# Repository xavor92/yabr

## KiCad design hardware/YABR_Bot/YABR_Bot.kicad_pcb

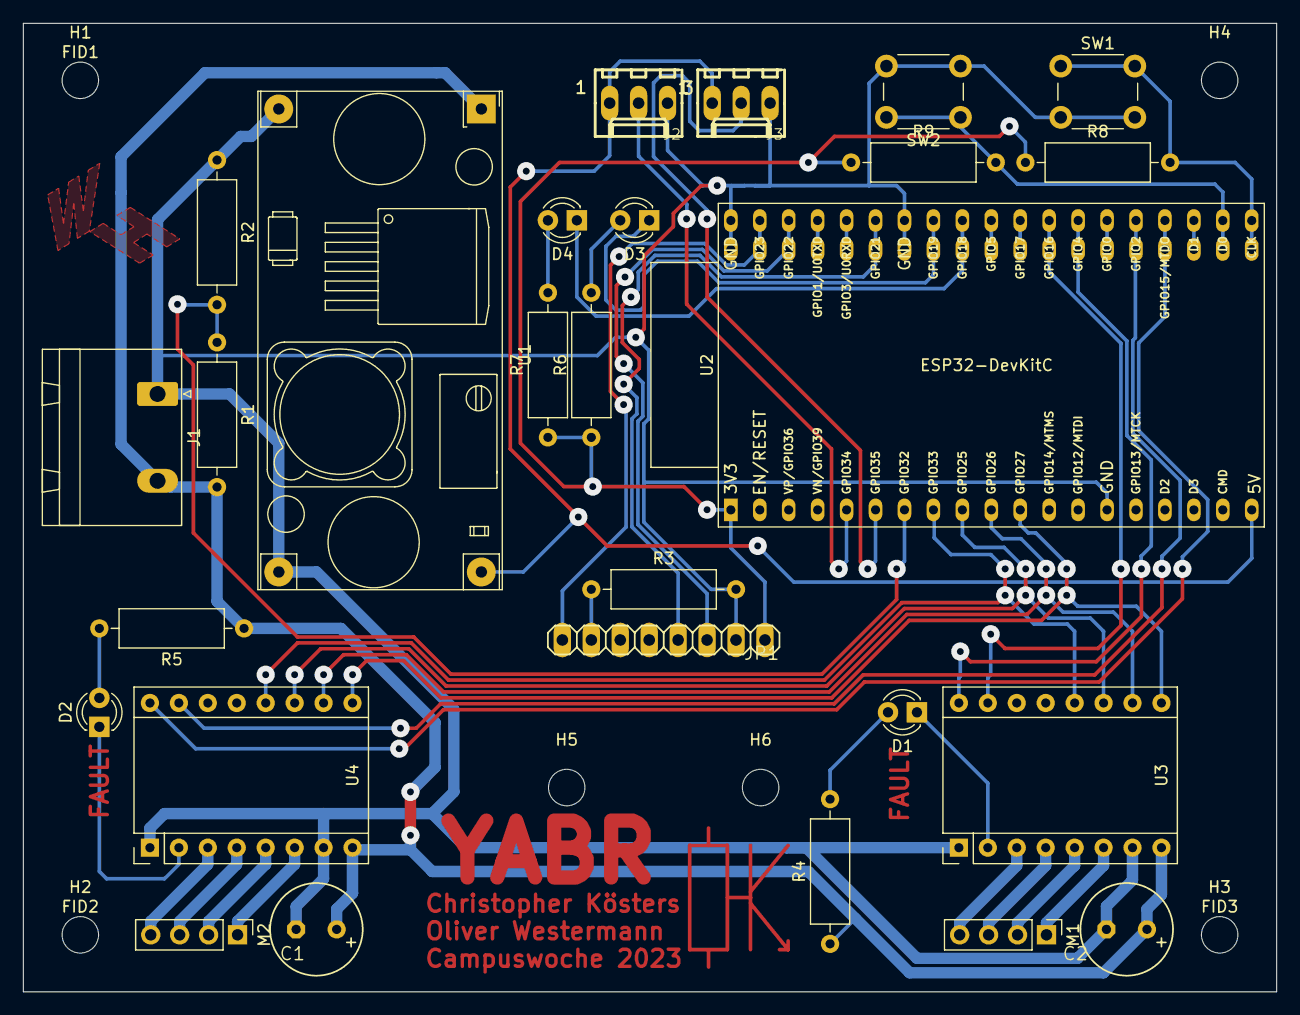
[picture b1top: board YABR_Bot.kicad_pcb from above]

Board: 2 copper layers, 110.0 x 85.0 mm, 36 parts (0 on the bottom side), 37 nets.

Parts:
C1, C2: 100uF/25V; E3,5-8
D1, D2, D3, D4: LED; LED_D3.0mm
FID1, FID2, FID3: Fiducial; Fiducial_1.5mm_Mask3mm
H1, H2, H3, H4, H5, H6: MountingHole; MountingHole_3.2mm_M3
J1: Conn_01x02_Socket; PhoenixContact_GMSTBA_2,5_2-G-7,62_1x02_P7.62mm_Horizontal
J2, J3: SERVO; 6410-03
JP1: ITG-MPU; 1X08
M1, M2: Stepper_Motor_bipolar; PinHeader_1x04_P2.54mm_Vertical
R1: 4k7; R_Axial_DIN0309_L9.0mm_D3.2mm_P12.70mm_Horizontal
R2: 3k3; R_Axial_DIN0309_L9.0mm_D3.2mm_P12.70mm_Horizontal
R3: 4K7; R_Axial_DIN0309_L9.0mm_D3.2mm_P12.70mm_Horizontal
R4, R5, R8, R9: 1K1; R_Axial_DIN0309_L9.0mm_D3.2mm_P12.70mm_Horizontal
R6, R7: 82; R_Axial_DIN0309_L9.0mm_D3.2mm_P12.70mm_Horizontal
SW1, SW2: SW_Push; SW_PUSH_6mm_H9.5mm
U1: DCDC_StepDown_LM2596
U2: ESP32-DevKitC
U3, U4: DRV8825; DRV8825_Breakout_15.2x20.3mm

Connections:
+3V3: JP1.1, R6.1, R7.1, R8.1, R9.1, U2.1 (3V3)
+5V: J2.1 (S), J3.1 (S), U1.4 (Vout), U2.19 (5V)
/AD0: JP1.7, R3.1
/DIR1: U2.26 (ADC2_CH0/GPIO4), U3.16 (DIR)
/DIR2: U2.23 (MTDO/GPIO15/ADC2_CH3), U4.16 (DIR)
/SCL: JP1.3, U2.36 (GPIO22)
/SDA: JP1.4, U2.33 (GPIO21)
/SERVO1: J2.2 (S), U2.5 (VDET_1/GPIO34/ADC1_CH6)
/SERVO2: J3.2 (S), U2.6 (VDET_2/GPIO35/ADC1_CH7)
/STEP_ENABLE: U2.11 (ADC2_CH7/GPIO27), U3.9 (EN), U4.9 (EN)
/STEP_SELECT_M0: U2.10 (DAC_2/ADC2_CH9/GPIO26), U3.10 (M0), U4.10 (M0)
/STEP_SELECT_M1: U2.9 (DAC_1/ADC2_CH8/GPIO25), U3.11 (M1), U4.11 (M1)
/STEP_SELECT_M2: U2.8 (32K_XN/GPIO33/ADC1_CH5), U3.12 (M2), U4.12 (M2)
/STP1: U2.27 (GPIO16), U3.15 (STP)
/STP2: U2.24 (ADC2_CH2/GPIO2), U4.15 (STP)
/VSENS: R1.1, R2.2, U2.7 (32K_XP/GPIO32/ADC1_CH4)
GND: C1.-, C2.-, J1.1, J2.3 (S), J3.3 (S), JP1.2, R2.1, R3.2, SW1.2, SW2.2, U1.2 (GND), U1.3 (GND), U2.14 (GND), U2.32 (GND), U2.38 (GND), U3.1 (GND), U3.7 (GND), U4.1 (GND), U4.7 (GND)
unnamed: D1.2 (A), R4.2
unnamed: D1.1 (K), U3.2 (FLT)
unnamed: D2.2 (A), R5.2
unnamed: D2.1 (K), U4.2 (FLT)
unnamed: D3.2 (A), R6.2
unnamed: D3.1 (K), U2.31 (GPIO19)
unnamed: D4.2 (A), R7.2
unnamed: D4.1 (K), U2.30 (GPIO18)
unnamed: M1.2 (-), U3.5 (B1)
unnamed: M2.2 (-), U4.5 (B1)
unnamed: JP1.8, U2.37 (GPIO23)
unnamed: R8.2, SW1.1, U2.20 (SD_CLK/GPIO6)
unnamed: R9.2, SW2.1, U2.21 (SD_DATA0/GPIO7)
unnamed: M1.3, U3.4 (A1)
unnamed: M1.4, U3.3 (A2)
unnamed: M1.1, U3.6 (B2)
unnamed: M2.3, U4.4 (A1)
unnamed: M2.4, U4.3 (A2)
unnamed: M2.1, U4.6 (B2)
VMOT: C1.+, C2.+, J1.2, R1.2, R4.1, R5.1, U1.1 (Vin), U3.8 (VMOT), U4.8 (VMOT)

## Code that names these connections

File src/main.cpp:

#include <Arduino.h>
#include <Adafruit_MPU6050.h>
#include <Adafruit_Sensor.h>
#include <Wire.h>
#include <ESPmDNS.h>
#include <WiFiUdp.h>
#include <ArduinoOTA.h>
#include <math.h>

// Fill and don't commit ;-)
const char* ssid = "ssid";
const char* password = "pw";

#define LEDC_CHANNEL_MOTOR1               1
#define LEDC_CHANNEL_MOTOR2               2
#define LEDC_CHANNEL_RESOLUTION_12_BIT    12
#define LEDC_CHANNEL_DUTY                 2048 // (2 ^ LEDC_CHANNEL_RESOLUTION_12_BIT) / 2
#define LEDC_CHANNEL_DEFAULT_SPEED        200

#define PIN_STEPPER_EN  27
#define PIN_STEP_SELECT_M0 26
#define PIN_STEP_SELECT_M1 25
#define PIN_STEP_SELECT_M2 33

#define PIN_DIR1    4
#define PIN_STEP1   16
#define PIN_DIR2    15
#define PIN_STEP2   2

#define PIN_LED1    19
#define PIN_LED2    18

#define PIN_BUTTON1 ERROR("Pin 6 can't be used")
#define PIN_BUTTON2 ERROR("Pin 7 can't be used")

#define PIN_ACC_INT 23

#define LEFT      0
#define RIGHT     1

/* Stop OTA after timeout */
#define OTA_TIMEOUT 15000

/* Permanent Z offset, set at boot */
float base_z = 0.00;

/* Controller setup */
float kP = 20000;

Adafruit_MPU6050 mpu;

void setup_ota() {
  WiFi.mode(WIFI_STA);
  WiFi.begin(ssid, password);
  while (WiFi.waitForConnectResult() != WL_CONNECTED) {
    Serial.println("Connection Failed! Rebooting...");
    delay(5000);
    ESP.restart();
  }
  Serial.println("Connected to wifi");

  ArduinoOTA
    .onStart([]() {
      String type;
      if (ArduinoOTA.getCommand() == U_FLASH)
        type = "sketch";
      else // U_SPIFFS
        type = "filesystem";

      // NOTE: if updating SPIFFS this would be the place to unmount SPIFFS using SPIFFS.end()
      Serial.println("Start updating " + type);
    })
    .onEnd([]() {
      Serial.println("\nEnd");
    })
    .onProgress([](unsigned int progress, unsigned int total) {
      Serial.printf("Progress: %u%%\r", (progress / (total / 100)));
    })
    .onError([](ota_error_t error) {
      Serial.printf("Error[%u]: ", error);
      if (error == OTA_AUTH_ERROR) Serial.println("Auth Failed");
      else if (error == OTA_BEGIN_ERROR) Serial.println("Begin Failed");
      else if (error == OTA_CONNECT_ERROR) Serial.println("Connect Failed");
      else if (error == OTA_RECEIVE_ERROR) Serial.println("Receive Failed");
      else if (error == OTA_END_ERROR) Serial.println("End Failed");
    });

  ArduinoOTA.begin();

  Serial.println("Ready");
  Serial.print("IP address: ");
  Serial.println(WiFi.localIP());
}

void setup_mpu6050() {
  if (!mpu.begin()) {
    Serial.println("Failed to find MPU6050 chip");
  }

  // setup MPU
  mpu.setAccelerometerRange(MPU6050_RANGE_2_G);
  Serial.print("Accelerometer range set to: ");
  switch (mpu.getAccelerometerRange()) {
  case MPU6050_RANGE_2_G:
    Serial.println("+-2G");
    break;
  case MPU6050_RANGE_4_G:
    Serial.println("+-4G");
    break;
  case MPU6050_RANGE_8_G:
    Serial.println("+-8G");
    break;
  case MPU6050_RANGE_16_G:
    Serial.println("+-16G");
    break;
  }

  mpu.setGyroRange(MPU6050_RANGE_250_DEG);
  Serial.print("Gyro range set to: ");
  switch (mpu.getGyroRange()) {
  case MPU6050_RANGE_250_DEG:
    Serial.println("+- 250 deg/s");
    break;
  case MPU6050_RANGE_500_DEG:
    Serial.println("+- 500 deg/s");
    break;
  case MPU6050_RANGE_1000_DEG:
    Serial.println("+- 1000 deg/s");
    break;
  case MPU6050_RANGE_2000_DEG:
    Serial.println("+- 2000 deg/s");
    break;
  }

  mpu.setFilterBandwidth(MPU6050_BAND_21_HZ);
  Serial.print("Filter bandwidth set to: ");
  switch (mpu.getFilterBandwidth()) {
  case MPU6050_BAND_260_HZ:
    Serial.println("260 Hz");
    break;
  case MPU6050_BAND_184_HZ:
    Serial.println("184 Hz");
    break;
  case MPU6050_BAND_94_HZ:
    Serial.println("94 Hz");
    break;
  case MPU6050_BAND_44_HZ:
    Serial.println("44 Hz");
    break;
  case MPU6050_BAND_21_HZ:
    Serial.println("21 Hz");
    break;
  case MPU6050_BAND_10_HZ:
    Serial.println("10 Hz");
    break;
  case MPU6050_BAND_5_HZ:
    Serial.println("5 Hz");
    break;
  }

  Serial.println("");
}

void setup_gpio() {
  // Setup pins for stepper driver
  pinMode(PIN_STEPPER_EN, OUTPUT);
  digitalWrite(PIN_STEPPER_EN, HIGH);

  pinMode(PIN_DIR1, OUTPUT);
  pinMode(PIN_DIR2, OUTPUT);

  pinMode(PIN_STEP1, OUTPUT);
  pinMode(PIN_STEP2, OUTPUT);

  ledcSetup(LEDC_CHANNEL_MOTOR1, LEDC_CHANNEL_DEFAULT_SPEED, LEDC_CHANNEL_RESOLUTION_12_BIT);
  ledcSetup(LEDC_CHANNEL_MOTOR2, LEDC_CHANNEL_DEFAULT_SPEED, LEDC_CHANNEL_RESOLUTION_12_BIT);

  ledcAttachPin(PIN_LED1, LEDC_CHANNEL_MOTOR1);
  ledcAttachPin(PIN_STEP1, LEDC_CHANNEL_MOTOR1);
  ledcAttachPin(PIN_STEP2, LEDC_CHANNEL_MOTOR2);

  ledcWrite(LEDC_CHANNEL_MOTOR1, LEDC_CHANNEL_DUTY);
  ledcWrite(LEDC_CHANNEL_MOTOR2, LEDC_CHANNEL_DUTY);

  pinMode(PIN_STEP_SELECT_M0, OUTPUT);
  pinMode(PIN_STEP_SELECT_M1, OUTPUT);
  pinMode(PIN_STEP_SELECT_M2, OUTPUT);
  digitalWrite(PIN_STEP_SELECT_M0, LOW);
  digitalWrite(PIN_STEP_SELECT_M1, LOW);
  digitalWrite(PIN_STEP_SELECT_M2, HIGH);

  pinMode(PIN_LED2, OUTPUT);
  digitalWrite(PIN_LED2, HIGH);
}

void setup() {
  Serial.begin(115200);

  setup_gpio();
  setup_ota();
  setup_mpu6050();
}

void print_step_stuff(unsigned int steps_per_second, unsigned int direction) {
  Serial.print("Starting rotation to ");
  if (direction != LEFT) {
    Serial.print("right ");
  } else {
    Serial.print("left ");
  }
  Serial.print("at ");
  Serial.print(steps_per_second);
  Serial.println(" steps/s");
}

void enable_motors() {
  digitalWrite(PIN_STEPPER_EN, LOW);
  digitalWrite(PIN_LED2, LOW);
}

void disable_motors() {
  digitalWrite(PIN_STEPPER_EN, HIGH);
  digitalWrite(PIN_LED2, HIGH);
}

void rotate(unsigned int steps_per_second, unsigned int direction) {
  uint32_t error, freq;
  uint8_t channel;

  if (!steps_per_second) {
      /* PWM can't handle freq of 0 */
#ifdef DEBUG
      Serial.println("steps_per_second is zero");
#endif
      return;
  }

  print_step_stuff(steps_per_second, direction);

  digitalWrite(PIN_DIR1, direction == LEFT);
  digitalWrite(PIN_DIR2, direction != LEFT);

  for(channel = 1; channel <= LEDC_CHANNEL_MOTOR2; channel++) {
    error = ledcChangeFrequency(channel, steps_per_second, LEDC_CHANNEL_RESOLUTION_12_BIT);
    if (!error) {
      Serial.print("Error on line ");
      Serial.println(__LINE__);
    } else {
#ifdef DEBUG
      Serial.print("Frequency on ");
      Serial.print(channel);
      Serial.print(" set to ");
      Serial.println(error);
#endif
    };
  }

  enable_motors();
}

float get_z_angle() {
  float z_angle, z_real;
  sensors_event_t a, g, temp;

  /* Get new sensor events with the readings */
  mpu.getEvent(&a, &g, &temp);

  /* Calculate a z angle */
  z_angle = atan(sqrt(a.acceleration.x * a.acceleration.x + a.acceleration.y * a.acceleration.y) / a.acceleration.z);

  /* Set a "base" orientation at startup */
  if (base_z <= 0.01 && base_z >= -0.01) {
    base_z = z_angle;
  }

  /* Rotate vector to have 0 pointing "upwards" with a range of -Pi/2 to Pi/2 */
  if (z_angle - base_z < -M_PI_2) {
    z_real = z_angle - base_z + M_PI;
  } else if (z_angle - base_z > M_PI_2) {
    z_real = z_angle - base_z - M_PI;
  } else {
    z_real = z_angle - base_z;
  }

#ifdef DEBUG
  Serial.print("z 'real': ");
  if (z_real < 0) { Serial.print("-"); } else { Serial.print(" "); };
  Serial.println(abs(z_real), 6);
#endif

  return z_real;
}

int control_function(float z_angle) {
  int steps_per_s = int32_t(kP * (z_angle));
  return steps_per_s;
}

void check_control_loop_speed() {
  static int cnt;
  static unsigned long current_second;
  cnt++;

  if (millis() / 1000 > current_second) {
    current_second = millis() / 1000;
    Serial.print("Last second had "); Serial.print(cnt); Serial.println("loops.");
    cnt = 0;
  }
}

void loop() {
  int32_t steps_per_s;
  float angle;

  check_control_loop_speed();

  if (millis() < OTA_TIMEOUT) {
    ArduinoOTA.handle();
  }

  angle = get_z_angle();

  steps_per_s = control_function(angle);

  rotate(abs(steps_per_s), steps_per_s < 0 ? RIGHT : LEFT);
}

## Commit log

2023-07-18 Add basic connectivity to MPU6050
2023-07-18 Replace own MPU implementation by library
2023-07-18 Setup OTA functionality
2023-07-18 Add first version of PCB
2023-07-19 Update Hardware to V2
2023-07-20 Ignore RT export files
2023-07-20 Remove & ignore kicad export data
2023-07-20 Rerouting
2023-07-20 Add hardware TODOs
2023-07-20 Add hardware todo for button pins
2023-07-20 Add Pin definitions
    Button pins are connected to SPI flash and unusable
2023-07-20 Select full step mode, enable motors
2023-07-20 Add basic PWM control
2023-07-21 Setup basic P controller
2023-07-21 Cleanup code a bit
2023-07-21 Cleanup code more, add control loop speed measurement
